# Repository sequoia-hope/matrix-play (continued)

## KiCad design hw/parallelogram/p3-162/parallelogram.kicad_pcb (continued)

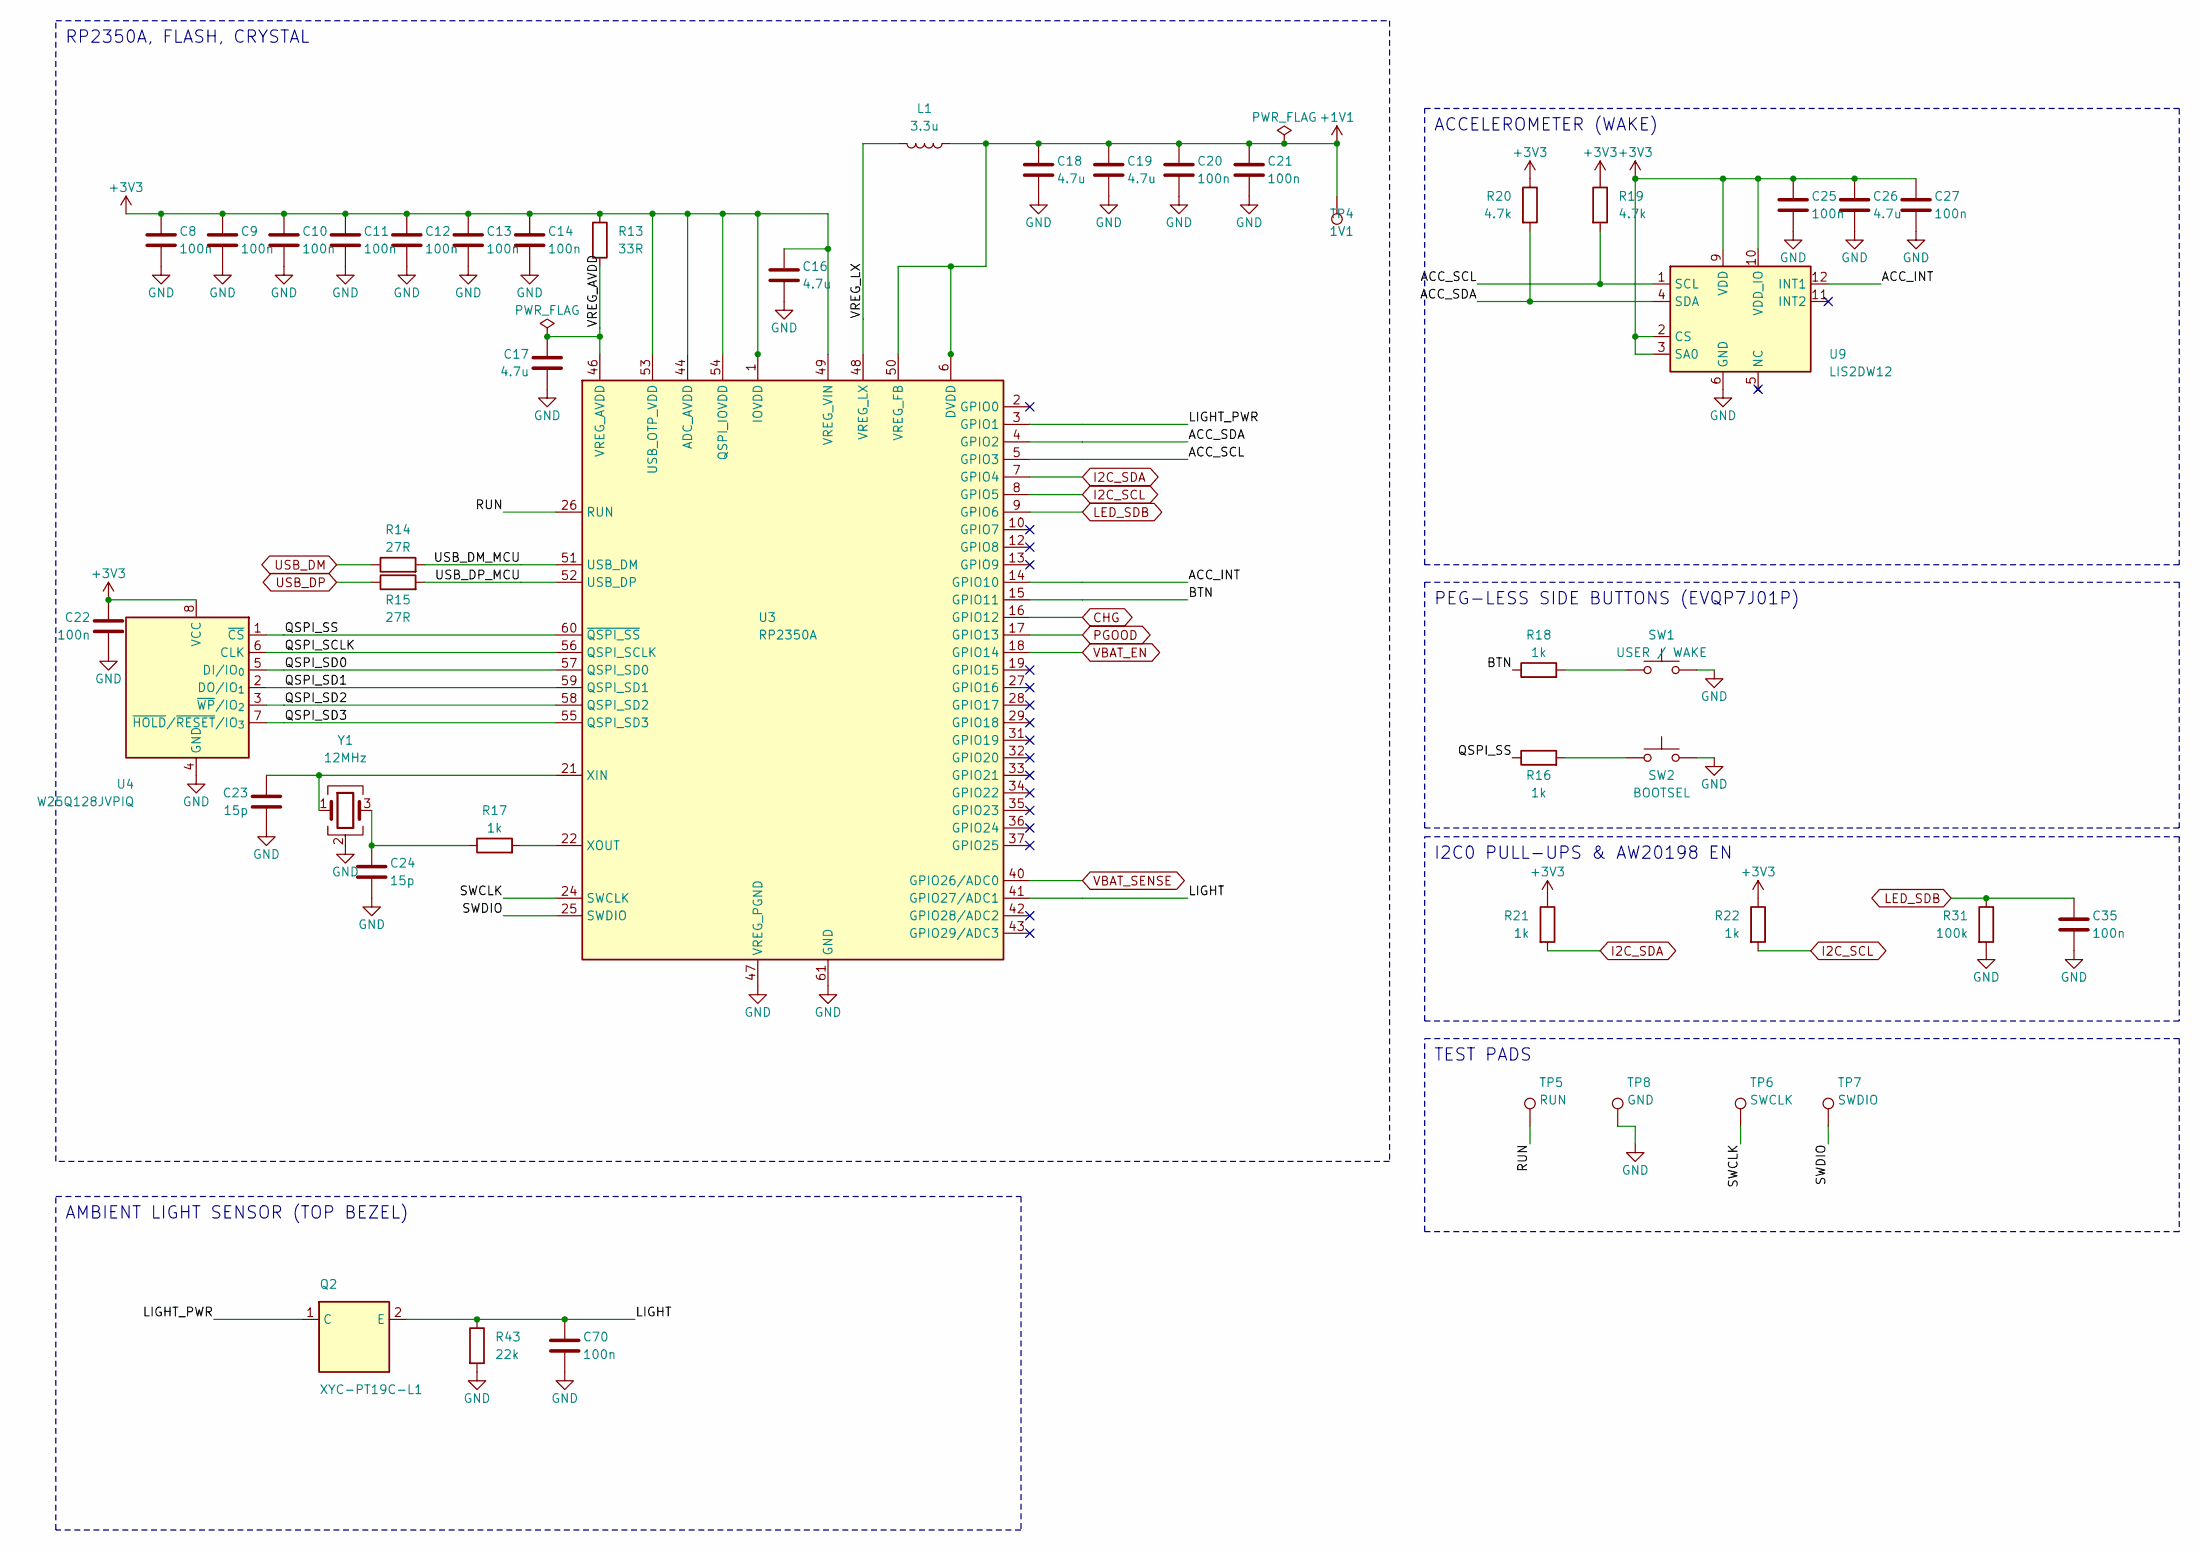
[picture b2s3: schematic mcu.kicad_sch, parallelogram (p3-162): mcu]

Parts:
C8, C9, C10, C11, C12, C13, C14, C20, C21, C22, C25, C27, C35, C70: 100n; C_0402_1005Metric; MPN CL05B104KO5NNNC; LCSC C1525
C16, C18: 4.7u; C_0402_1005Metric_small_pads; MPN CL05A475MP5NRNC; LCSC C23733
C17, C19, C26: 4.7u; C_0402_1005Metric; MPN CL05A475MP5NRNC; LCSC C23733
C23, C24: 15p; C_0402_1005Metric; MPN 0402CG150J500NT; LCSC C1548
L1: 3.3u; L_pol_2016; MPN AOTA-B201610S3R3-101-T; LCSC C42411119
Q2: XYC-PT19C-L1; SENSOR_ALS-PT19; MPN XYC-PT19C-L1; LCSC C2693594
R13: 33R; R_0402_1005Metric; MPN 0402WGF330JTCE; LCSC C25105
R14, R15: 27R; R_0402_1005Metric; MPN 0402WGF270JTCE; LCSC C25100
R16, R17, R18, R21, R22: 1k; R_0402_1005Metric; MPN 0402WGF1001TCE; LCSC C11702
R19, R20: 4.7k; R_0402_1005Metric; MPN 0402WGF4701TCE; LCSC C25900
R31: 100k; R_0402_1005Metric; MPN 0402WGF1003TCE; LCSC C25741
R43: 22k; R_0402_1005Metric; MPN 0402WGF2202TCE; LCSC C25768
SW1: USER / WAKE; SW_Panasonic_EVQP7J; MPN EVQP7J01P; LCSC C2828254
SW2: BOOTSEL; SW_Panasonic_EVQP7J; MPN EVQP7J01P; LCSC C2828254
TP4: 1V1; TestPoint_Pad_D1.0mm
TP5: RUN; TestPoint_Pad_D1.0mm
TP6: SWCLK; TestPoint_Pad_D1.0mm
TP7: SWDIO; TestPoint_Pad_D1.0mm
TP8: GND; TestPoint_Pad_D1.0mm
U3: RP2350A; RP2350-QFN-60-1EP_7x7_P0.4mm_EP3.4x3.4mm_ThermalVias; MPN RP2350A; LCSC C42411118
U4: W25Q128JVPIQ; WSON-8_6x5mm_P1.27mm_NoEPCopper; MPN W25Q128JVPIQ; LCSC C190862
U9: LIS2DW12; LGA-12_2x2mm_P0.5mm; MPN LIS2DW12TR; LCSC C189624
Y1: 12MHz; Crystal_SMD_3225-4Pin_3.2x2.5mm; MPN ABM8-272-T3; LCSC C20625731

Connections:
+3V3: C8.1, C9.1, C10.1, C11.1, C12.1, C13.1, C14.1, C16.1, C22.1, C25.1, C26.1, C27.1, R13.1, R19.1, R20.1, R21.1, R22.1, U3.1 (IOVDD), U3.11 (IOVDD), U3.20 (IOVDD), U3.30 (IOVDD), U3.38 (IOVDD), U3.44 (ADC_AVDD), U3.45 (IOVDD), U3.49 (VREG_VIN), U3.53 (USB_OTP_VDD), U3.54 (QSPI_IOVDD), U4.8 (VCC), U9.2 (CS), U9.3 (SA0), U9.9 (VDD), U9.10 (VDD_IO); also elsewhere on the board
/MCU/ACC_INT: U3.14 (GPIO10), U9.12 (INT1)
/MCU/ACC_SCL: R19.2, U3.5 (GPIO3), U9.1 (SCL)
/MCU/ACC_SDA: R20.2, U3.4 (GPIO2), U9.4 (SDA)
/MCU/BTN: R18.1, U3.15 (GPIO11)
/MCU/LIGHT: C70.1, Q2.2 (E), R43.1, U3.41 (GPIO27/ADC1)
/MCU/LIGHT_PWR: Q2.1 (C), U3.3 (GPIO1)
/MCU/QSPI_SCLK: U3.56 (QSPI_SCLK), U4.6 (CLK)
/MCU/QSPI_SD0: U3.57 (QSPI_SD0), U4.5 (DI/IO_{0})
/MCU/QSPI_SD1: U3.59 (QSPI_SD1), U4.2 (DO/IO_{1})
/MCU/QSPI_SD2: U3.58 (QSPI_SD2), U4.3 (~WP/IO_{2})
/MCU/QSPI_SD3: U3.55 (QSPI_SD3), U4.7 (~HOLD/~RESET/IO_{3})
/MCU/QSPI_SS: R16.1, U3.60 (~QSPI_SS), U4.1 (~CS)
/MCU/RUN: TP5.1, U3.26 (RUN)
/MCU/SWCLK: TP6.1, U3.24 (SWCLK)
/MCU/SWDIO: TP7.1, U3.25 (SWDIO)
/MCU/USB_DM_MCU: R14.2, U3.51 (USB_DM)
/MCU/USB_DP_MCU: R15.2, U3.52 (USB_DP)
/MCU/VREG_LX: L1.2, U3.48 (VREG_LX)
CHG: U3.16 (GPIO12); also elsewhere on the board
I2C_SCL: R22.2, U3.8 (GPIO5); also elsewhere on the board
I2C_SDA: R21.2, U3.7 (GPIO4); also elsewhere on the board
LED_SDB: C35.1, R31.1, U3.9 (GPIO6); also elsewhere on the board
unnamed: C24.1, R17.1, Y1.3
unnamed: R16.2, SW2.1
unnamed: R18.2, SW1.1
unnamed: C23.1, U3.21 (XIN), Y1.1
unnamed: R17.2, U3.22 (XOUT)
PGOOD: U3.17 (GPIO13); also elsewhere on the board
USB_DM: R14.1; also elsewhere on the board
USB_DP: R15.1; also elsewhere on the board
VBAT_EN: U3.18 (GPIO14); also elsewhere on the board
VBAT_SENSE: U3.40 (GPIO26/ADC0); also elsewhere on the board

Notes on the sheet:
RP2350A, FLASH, CRYSTAL
ACCELEROMETER (WAKE)
PEG-LESS SIDE BUTTONS (EVQP7J01P)
I2C0 PULL-UPS & AW20198 EN
TEST PADS
AMBIENT LIGHT SENSOR (TOP BEZEL)

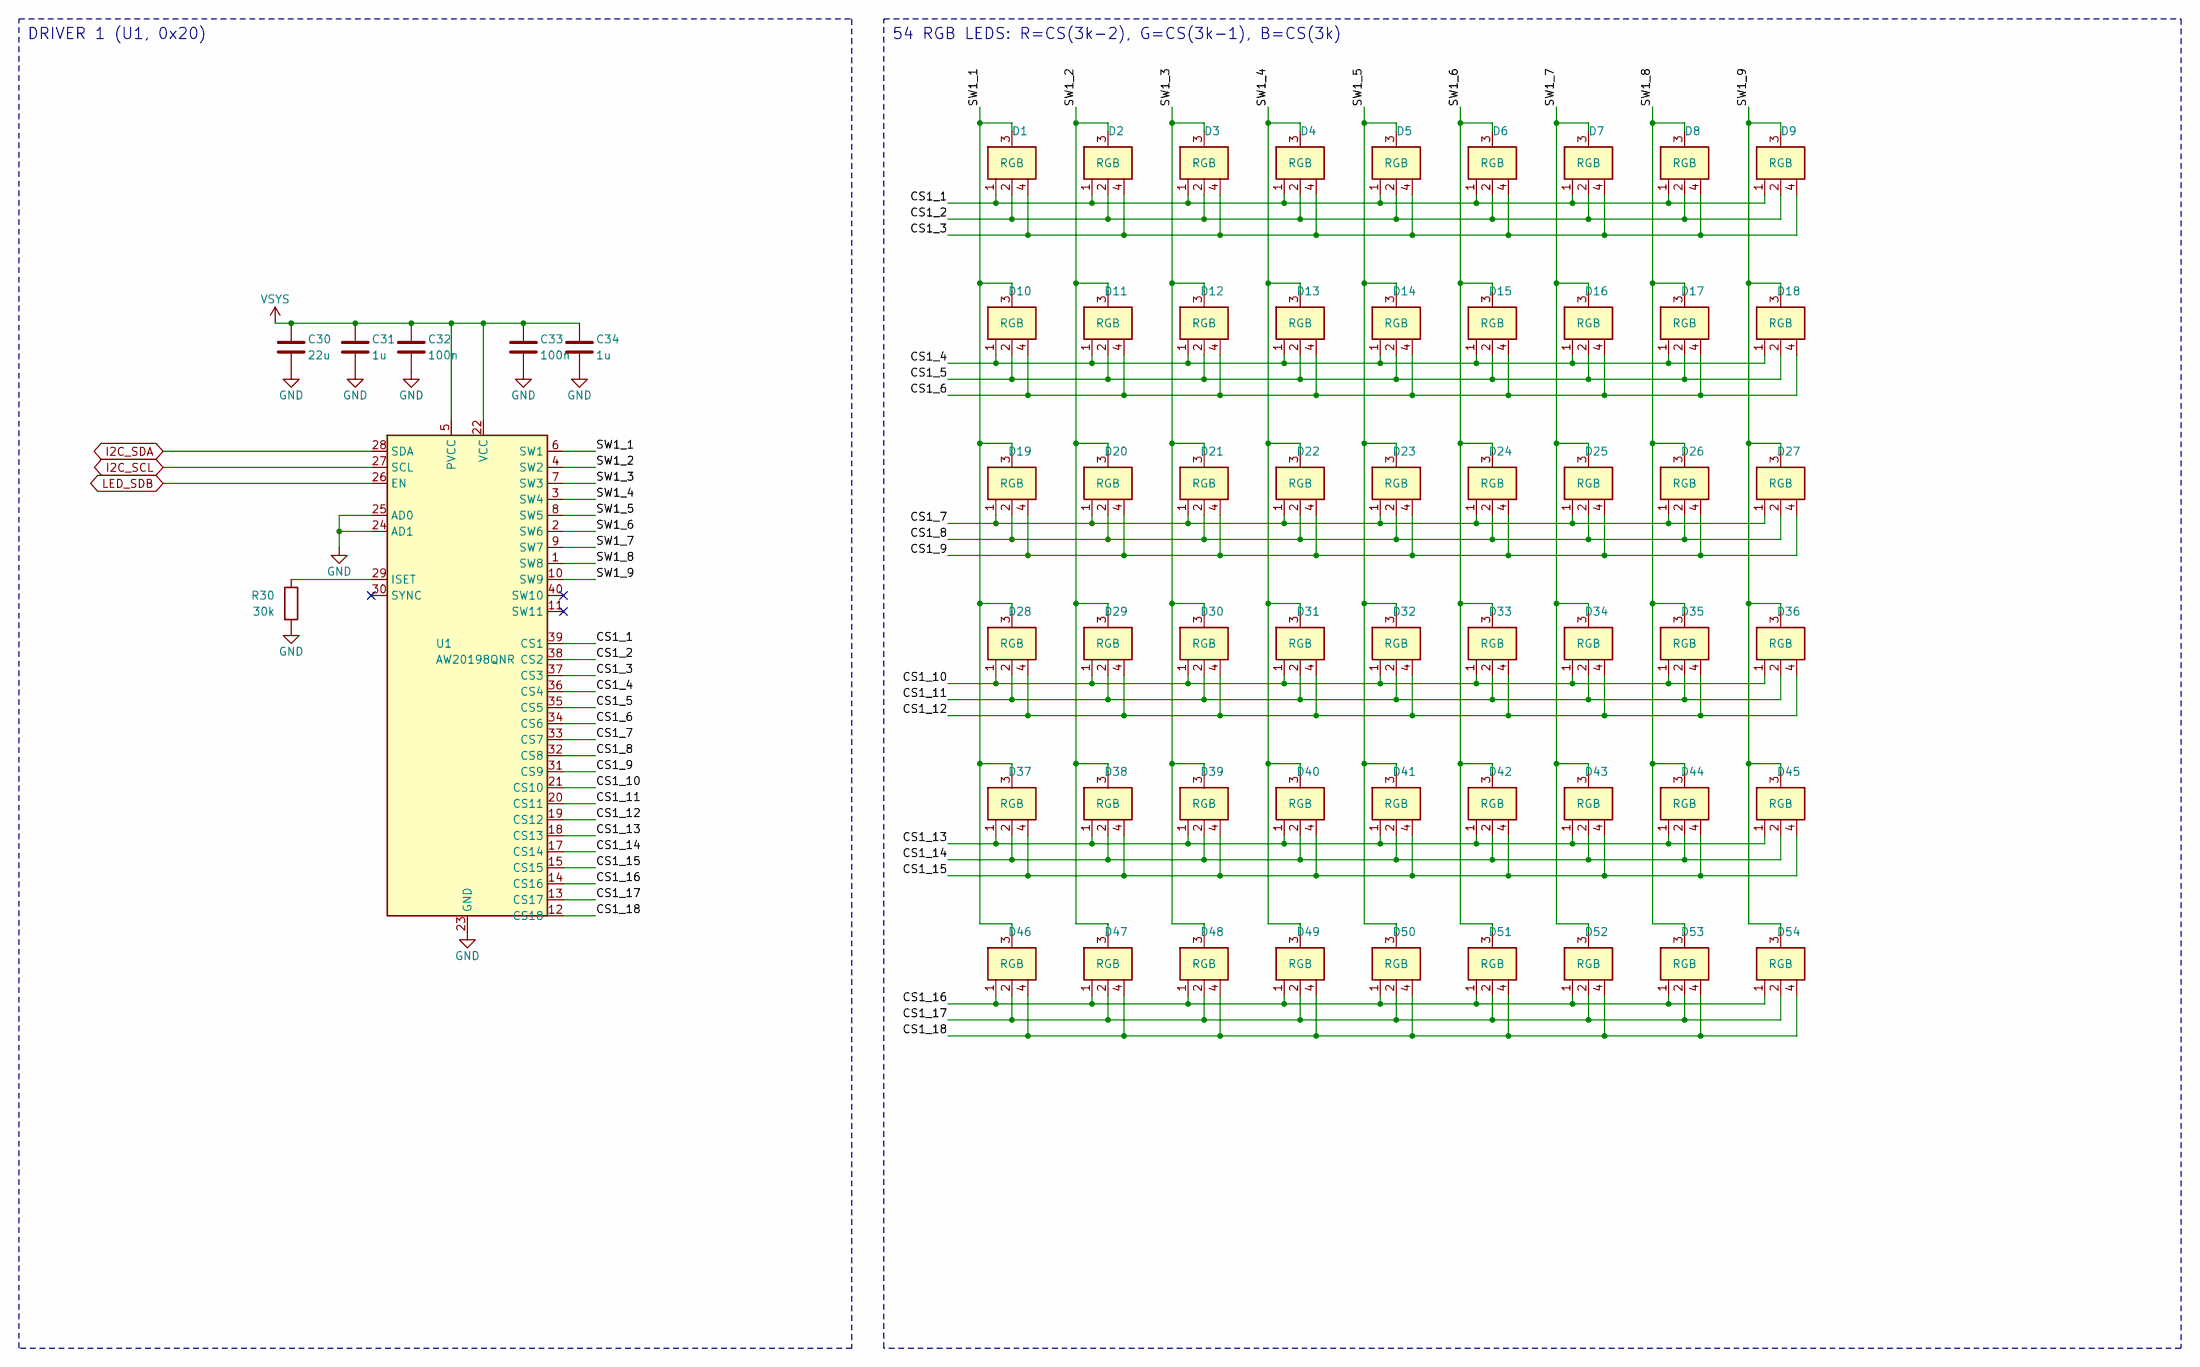
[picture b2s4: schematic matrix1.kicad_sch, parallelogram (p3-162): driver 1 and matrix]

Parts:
C30: 22u; C_0603_1608Metric; MPN CL10A226MP8NUNE; LCSC C86295
C31, C34: 1u; C_0402_1005Metric; MPN CL05A105KA5NQNC; LCSC C52923
C32, C33: 100n; C_0402_1005Metric; MPN CL05B104KO5NNNC; LCSC C1525
D1, D2, D3, D4, D5, D6, D7, D8, D9, D10, D11, D12, D13, D14, D15, D16, D17, D18, D19, D20, D21, D22, D23, D24, D25, D26, D27, D28, D29, D30, D31, D32, D33, D34, D35, D36, D37, D38, D39, D40, D41, D42, D43, D44, D45, D46, D47, D48, D49, D50, D51, D52, D53, D54: RGB; LED_XL-1010RGB; MPN XL-1010RGB-YG; LCSC C965834
R30: 30k; R_0402_1005Metric; MPN 0402WGF3002TCE; LCSC C25776
U1: AW20198QNR; AW20198_QFN-40-1EP_5x5mm_P0.4mm_EP3.4x3.4mm; MPN AW20198QNR; LCSC C5137654

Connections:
/Driver 1 and matrix/CS1_1: D1.1 (R), D2.1 (R), D3.1 (R), D4.1 (R), D5.1 (R), D6.1 (R), D7.1 (R), D8.1 (R), D9.1 (R), U1.39 (CS1)
/Driver 1 and matrix/CS1_2: D1.2 (G), D2.2 (G), D3.2 (G), D4.2 (G), D5.2 (G), D6.2 (G), D7.2 (G), D8.2 (G), D9.2 (G), U1.38 (CS2)
/Driver 1 and matrix/CS1_3: D1.4 (B), D2.4 (B), D3.4 (B), D4.4 (B), D5.4 (B), D6.4 (B), D7.4 (B), D8.4 (B), D9.4 (B), U1.37 (CS3)
/Driver 1 and matrix/CS1_4: D10.1 (R), D11.1 (R), D12.1 (R), D13.1 (R), D14.1 (R), D15.1 (R), D16.1 (R), D17.1 (R), D18.1 (R), U1.36 (CS4)
/Driver 1 and matrix/CS1_5: D10.2 (G), D11.2 (G), D12.2 (G), D13.2 (G), D14.2 (G), D15.2 (G), D16.2 (G), D17.2 (G), D18.2 (G), U1.35 (CS5)
/Driver 1 and matrix/CS1_6: D10.4 (B), D11.4 (B), D12.4 (B), D13.4 (B), D14.4 (B), D15.4 (B), D16.4 (B), D17.4 (B), D18.4 (B), U1.34 (CS6)
/Driver 1 and matrix/CS1_7: D19.1 (R), D20.1 (R), D21.1 (R), D22.1 (R), D23.1 (R), D24.1 (R), D25.1 (R), D26.1 (R), D27.1 (R), U1.33 (CS7)
/Driver 1 and matrix/CS1_8: D19.2 (G), D20.2 (G), D21.2 (G), D22.2 (G), D23.2 (G), D24.2 (G), D25.2 (G), D26.2 (G), D27.2 (G), U1.32 (CS8)
/Driver 1 and matrix/CS1_9: D19.4 (B), D20.4 (B), D21.4 (B), D22.4 (B), D23.4 (B), D24.4 (B), D25.4 (B), D26.4 (B), D27.4 (B), U1.31 (CS9)
/Driver 1 and matrix/CS1_10: D28.1 (R), D29.1 (R), D30.1 (R), D31.1 (R), D32.1 (R), D33.1 (R), D34.1 (R), D35.1 (R), D36.1 (R), U1.21 (CS10)
/Driver 1 and matrix/CS1_11: D28.2 (G), D29.2 (G), D30.2 (G), D31.2 (G), D32.2 (G), D33.2 (G), D34.2 (G), D35.2 (G), D36.2 (G), U1.20 (CS11)
/Driver 1 and matrix/CS1_12: D28.4 (B), D29.4 (B), D30.4 (B), D31.4 (B), D32.4 (B), D33.4 (B), D34.4 (B), D35.4 (B), D36.4 (B), U1.19 (CS12)
/Driver 1 and matrix/CS1_13: D37.1 (R), D38.1 (R), D39.1 (R), D40.1 (R), D41.1 (R), D42.1 (R), D43.1 (R), D44.1 (R), D45.1 (R), U1.18 (CS13)
/Driver 1 and matrix/CS1_14: D37.2 (G), D38.2 (G), D39.2 (G), D40.2 (G), D41.2 (G), D42.2 (G), D43.2 (G), D44.2 (G), D45.2 (G), U1.17 (CS14)
/Driver 1 and matrix/CS1_15: D37.4 (B), D38.4 (B), D39.4 (B), D40.4 (B), D41.4 (B), D42.4 (B), D43.4 (B), D44.4 (B), D45.4 (B), U1.15 (CS15)
/Driver 1 and matrix/CS1_16: D46.1 (R), D47.1 (R), D48.1 (R), D49.1 (R), D50.1 (R), D51.1 (R), D52.1 (R), D53.1 (R), D54.1 (R), U1.14 (CS16)
/Driver 1 and matrix/CS1_17: D46.2 (G), D47.2 (G), D48.2 (G), D49.2 (G), D50.2 (G), D51.2 (G), D52.2 (G), D53.2 (G), D54.2 (G), U1.13 (CS17)
/Driver 1 and matrix/CS1_18: D46.4 (B), D47.4 (B), D48.4 (B), D49.4 (B), D50.4 (B), D51.4 (B), D52.4 (B), D53.4 (B), D54.4 (B), U1.12 (CS18)
/Driver 1 and matrix/SW1_1: D1.3 (A), D10.3 (A), D19.3 (A), D28.3 (A), D37.3 (A), D46.3 (A), U1.6 (SW1)
/Driver 1 and matrix/SW1_2: D2.3 (A), D11.3 (A), D20.3 (A), D29.3 (A), D38.3 (A), D47.3 (A), U1.4 (SW2)
/Driver 1 and matrix/SW1_3: D3.3 (A), D12.3 (A), D21.3 (A), D30.3 (A), D39.3 (A), D48.3 (A), U1.7 (SW3)
/Driver 1 and matrix/SW1_4: D4.3 (A), D13.3 (A), D22.3 (A), D31.3 (A), D40.3 (A), D49.3 (A), U1.3 (SW4)
/Driver 1 and matrix/SW1_5: D5.3 (A), D14.3 (A), D23.3 (A), D32.3 (A), D41.3 (A), D50.3 (A), U1.8 (SW5)
/Driver 1 and matrix/SW1_6: D6.3 (A), D15.3 (A), D24.3 (A), D33.3 (A), D42.3 (A), D51.3 (A), U1.2 (SW6)
/Driver 1 and matrix/SW1_7: D7.3 (A), D16.3 (A), D25.3 (A), D34.3 (A), D43.3 (A), D52.3 (A), U1.9 (SW7)
/Driver 1 and matrix/SW1_8: D8.3 (A), D17.3 (A), D26.3 (A), D35.3 (A), D44.3 (A), D53.3 (A), U1.1 (SW8)
/Driver 1 and matrix/SW1_9: D9.3 (A), D18.3 (A), D27.3 (A), D36.3 (A), D45.3 (A), D54.3 (A), U1.10 (SW9)
I2C_SCL: U1.27 (SCL); also elsewhere on the board
I2C_SDA: U1.28 (SDA); also elsewhere on the board
LED_SDB: U1.26 (EN); also elsewhere on the board
unnamed: R30.1, U1.29 (ISET)
VSYS: C30.1, C31.1, C32.1, C33.1, C34.1, U1.5 (PVCC), U1.22 (VCC); also elsewhere on the board

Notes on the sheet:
DRIVER 1 (U1, 0x20)
54 RGB LEDS: R=CS(3k-2), G=CS(3k-1), B=CS(3k)

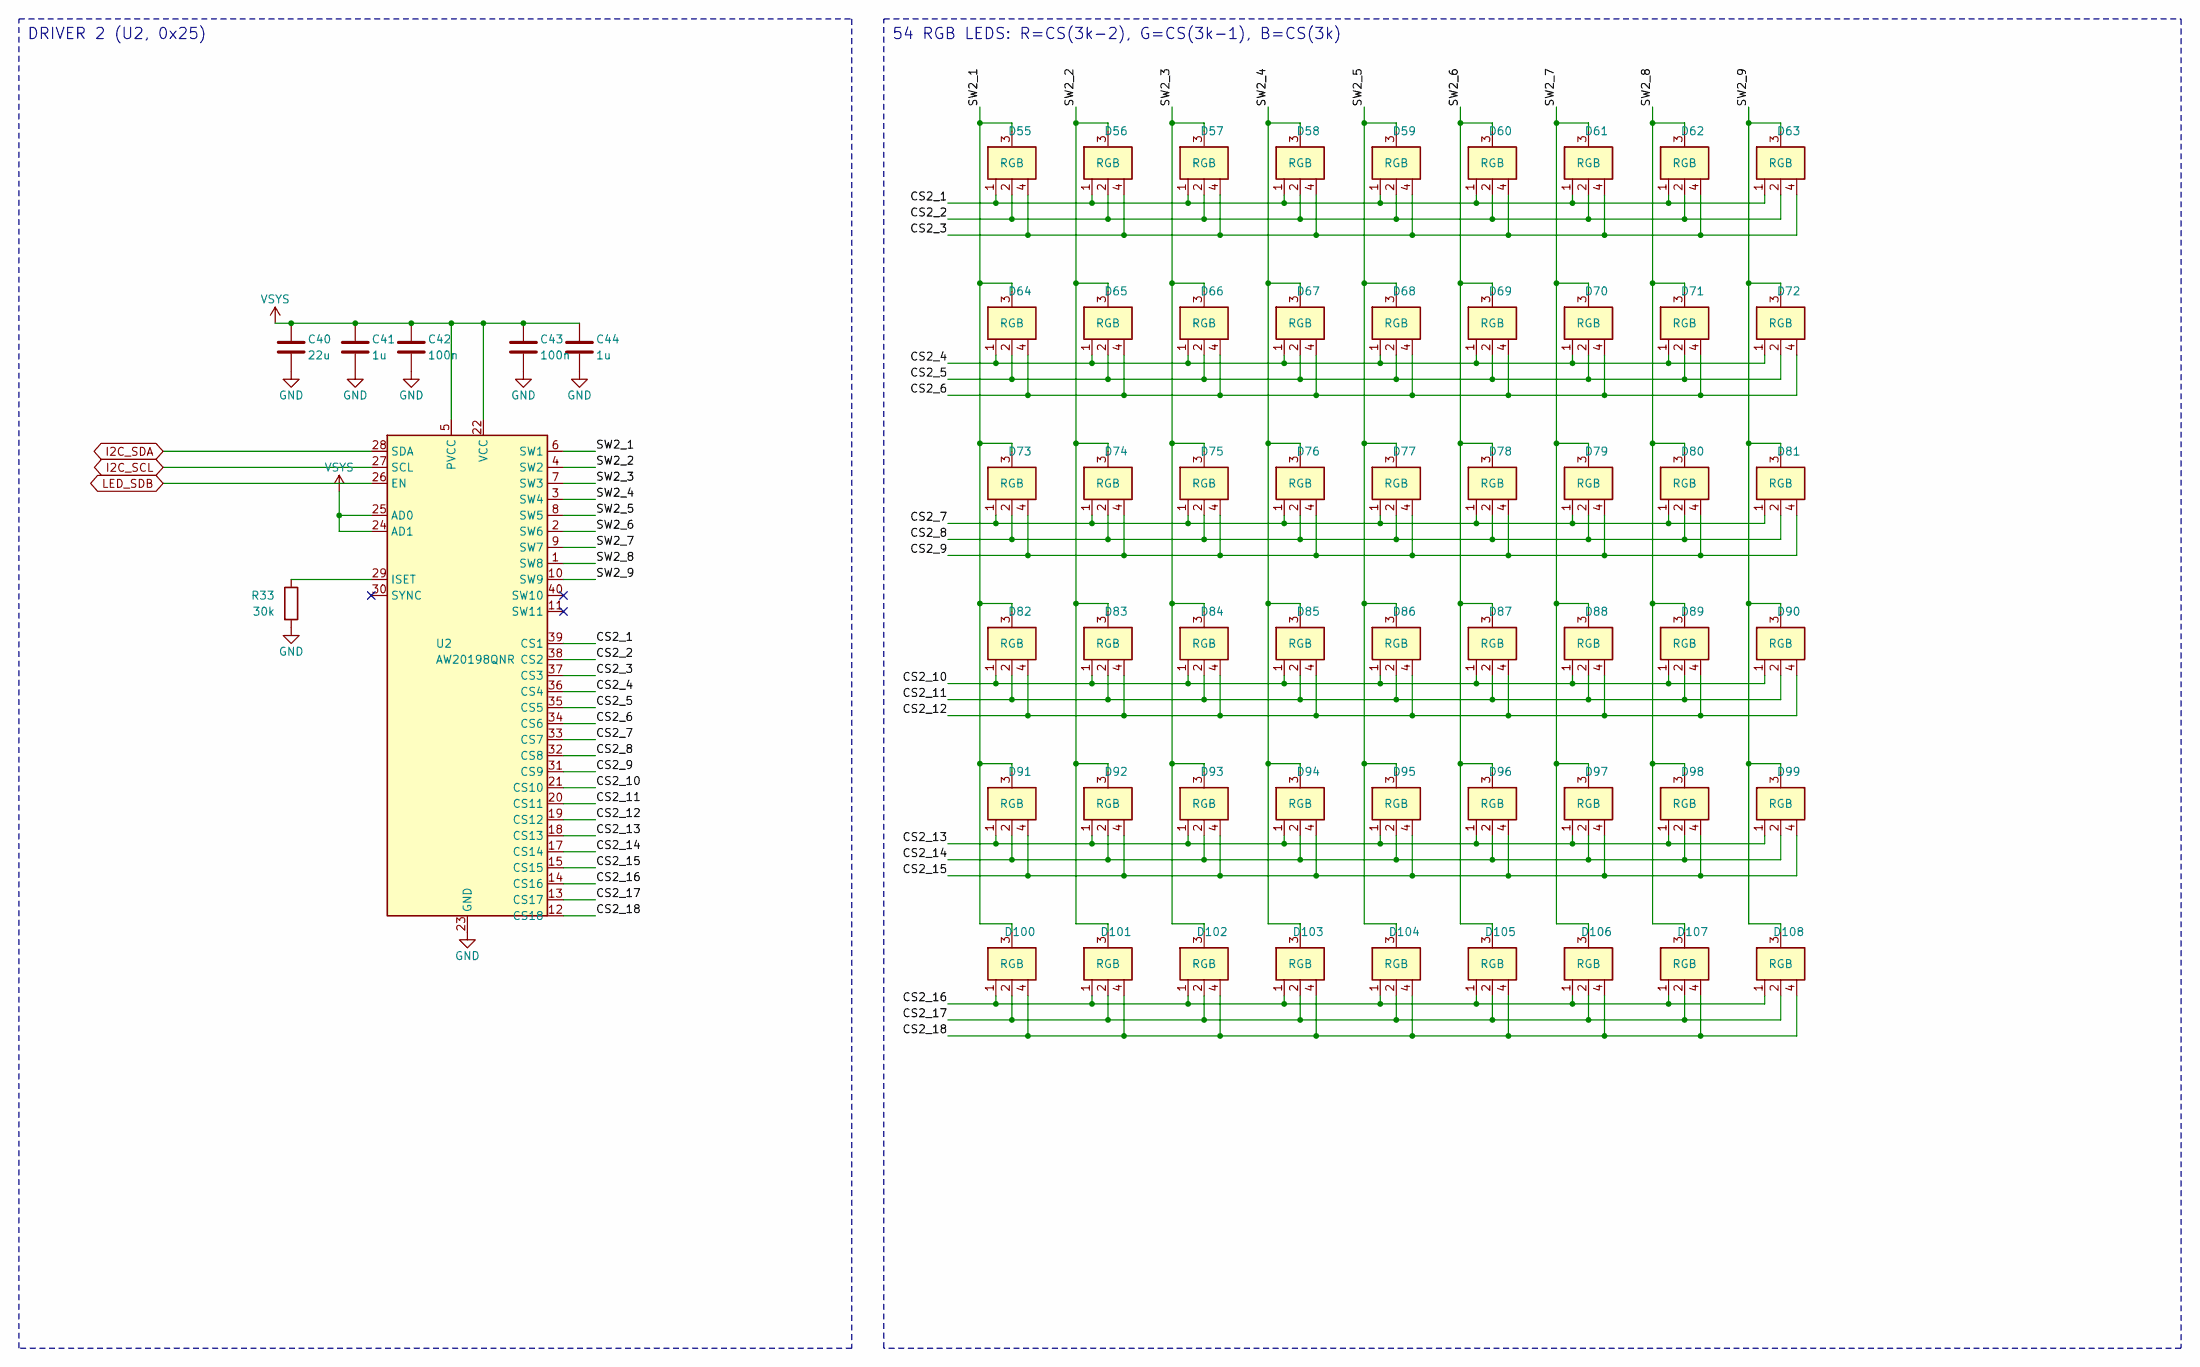
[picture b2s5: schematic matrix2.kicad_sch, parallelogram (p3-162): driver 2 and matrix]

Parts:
C40: 22u; C_0603_1608Metric; MPN CL10A226MP8NUNE; LCSC C86295
C41, C44: 1u; C_0402_1005Metric; MPN CL05A105KA5NQNC; LCSC C52923
C42, C43: 100n; C_0402_1005Metric; MPN CL05B104KO5NNNC; LCSC C1525
D55, D56, D57, D58, D59, D60, D61, D62, D63, D64, D65, D66, D67, D68, D69, D70, D71, D72, D73, D74, D75, D76, D77, D78, D79, D80, D81, D82, D83, D84, D85, D86, D87, D88, D89, D90, D91, D92, D93, D94, D95, D96, D97, D98, D99, D100, D101, D102, D103, D104, D105, D106, D107, D108: RGB; LED_XL-1010RGB; MPN XL-1010RGB-YG; LCSC C965834
R33: 30k; R_0402_1005Metric; MPN 0402WGF3002TCE; LCSC C25776
U2: AW20198QNR; AW20198_QFN-40-1EP_5x5mm_P0.4mm_EP3.4x3.4mm; MPN AW20198QNR; LCSC C5137654

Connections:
/Driver 2 and matrix/CS2_1: D55.1 (R), D56.1 (R), D57.1 (R), D58.1 (R), D59.1 (R), D60.1 (R), D61.1 (R), D62.1 (R), D63.1 (R), U2.39 (CS1)
/Driver 2 and matrix/CS2_2: D55.2 (G), D56.2 (G), D57.2 (G), D58.2 (G), D59.2 (G), D60.2 (G), D61.2 (G), D62.2 (G), D63.2 (G), U2.38 (CS2)
/Driver 2 and matrix/CS2_3: D55.4 (B), D56.4 (B), D57.4 (B), D58.4 (B), D59.4 (B), D60.4 (B), D61.4 (B), D62.4 (B), D63.4 (B), U2.37 (CS3)
/Driver 2 and matrix/CS2_4: D64.1 (R), D65.1 (R), D66.1 (R), D67.1 (R), D68.1 (R), D69.1 (R), D70.1 (R), D71.1 (R), D72.1 (R), U2.36 (CS4)
/Driver 2 and matrix/CS2_5: D64.2 (G), D65.2 (G), D66.2 (G), D67.2 (G), D68.2 (G), D69.2 (G), D70.2 (G), D71.2 (G), D72.2 (G), U2.35 (CS5)
/Driver 2 and matrix/CS2_6: D64.4 (B), D65.4 (B), D66.4 (B), D67.4 (B), D68.4 (B), D69.4 (B), D70.4 (B), D71.4 (B), D72.4 (B), U2.34 (CS6)
/Driver 2 and matrix/CS2_7: D73.1 (R), D74.1 (R), D75.1 (R), D76.1 (R), D77.1 (R), D78.1 (R), D79.1 (R), D80.1 (R), D81.1 (R), U2.33 (CS7)
/Driver 2 and matrix/CS2_8: D73.2 (G), D74.2 (G), D75.2 (G), D76.2 (G), D77.2 (G), D78.2 (G), D79.2 (G), D80.2 (G), D81.2 (G), U2.32 (CS8)
/Driver 2 and matrix/CS2_9: D73.4 (B), D74.4 (B), D75.4 (B), D76.4 (B), D77.4 (B), D78.4 (B), D79.4 (B), D80.4 (B), D81.4 (B), U2.31 (CS9)
/Driver 2 and matrix/CS2_10: D82.1 (R), D83.1 (R), D84.1 (R), D85.1 (R), D86.1 (R), D87.1 (R), D88.1 (R), D89.1 (R), D90.1 (R), U2.21 (CS10)
/Driver 2 and matrix/CS2_11: D82.2 (G), D83.2 (G), D84.2 (G), D85.2 (G), D86.2 (G), D87.2 (G), D88.2 (G), D89.2 (G), D90.2 (G), U2.20 (CS11)
/Driver 2 and matrix/CS2_12: D82.4 (B), D83.4 (B), D84.4 (B), D85.4 (B), D86.4 (B), D87.4 (B), D88.4 (B), D89.4 (B), D90.4 (B), U2.19 (CS12)
/Driver 2 and matrix/CS2_13: D91.1 (R), D92.1 (R), D93.1 (R), D94.1 (R), D95.1 (R), D96.1 (R), D97.1 (R), D98.1 (R), D99.1 (R), U2.18 (CS13)
/Driver 2 and matrix/CS2_14: D91.2 (G), D92.2 (G), D93.2 (G), D94.2 (G), D95.2 (G), D96.2 (G), D97.2 (G), D98.2 (G), D99.2 (G), U2.17 (CS14)
/Driver 2 and matrix/CS2_15: D91.4 (B), D92.4 (B), D93.4 (B), D94.4 (B), D95.4 (B), D96.4 (B), D97.4 (B), D98.4 (B), D99.4 (B), U2.15 (CS15)
/Driver 2 and matrix/CS2_16: D100.1 (R), D101.1 (R), D102.1 (R), D103.1 (R), D104.1 (R), D105.1 (R), D106.1 (R), D107.1 (R), D108.1 (R), U2.14 (CS16)
/Driver 2 and matrix/CS2_17: D100.2 (G), D101.2 (G), D102.2 (G), D103.2 (G), D104.2 (G), D105.2 (G), D106.2 (G), D107.2 (G), D108.2 (G), U2.13 (CS17)
/Driver 2 and matrix/CS2_18: D100.4 (B), D101.4 (B), D102.4 (B), D103.4 (B), D104.4 (B), D105.4 (B), D106.4 (B), D107.4 (B), D108.4 (B), U2.12 (CS18)
/Driver 2 and matrix/SW2_1: D55.3 (A), D64.3 (A), D73.3 (A), D82.3 (A), D91.3 (A), D100.3 (A), U2.6 (SW1)
/Driver 2 and matrix/SW2_2: D56.3 (A), D65.3 (A), D74.3 (A), D83.3 (A), D92.3 (A), D101.3 (A), U2.4 (SW2)
/Driver 2 and matrix/SW2_3: D57.3 (A), D66.3 (A), D75.3 (A), D84.3 (A), D93.3 (A), D102.3 (A), U2.7 (SW3)
/Driver 2 and matrix/SW2_4: D58.3 (A), D67.3 (A), D76.3 (A), D85.3 (A), D94.3 (A), D103.3 (A), U2.3 (SW4)
/Driver 2 and matrix/SW2_5: D59.3 (A), D68.3 (A), D77.3 (A), D86.3 (A), D95.3 (A), D104.3 (A), U2.8 (SW5)
/Driver 2 and matrix/SW2_6: D60.3 (A), D69.3 (A), D78.3 (A), D87.3 (A), D96.3 (A), D105.3 (A), U2.2 (SW6)
/Driver 2 and matrix/SW2_7: D61.3 (A), D70.3 (A), D79.3 (A), D88.3 (A), D97.3 (A), D106.3 (A), U2.9 (SW7)
/Driver 2 and matrix/SW2_8: D62.3 (A), D71.3 (A), D80.3 (A), D89.3 (A), D98.3 (A), D107.3 (A), U2.1 (SW8)
/Driver 2 and matrix/SW2_9: D63.3 (A), D72.3 (A), D81.3 (A), D90.3 (A), D99.3 (A), D108.3 (A), U2.10 (SW9)
I2C_SCL: U2.27 (SCL); also elsewhere on the board
I2C_SDA: U2.28 (SDA); also elsewhere on the board
LED_SDB: U2.26 (EN); also elsewhere on the board
unnamed: R33.1, U2.29 (ISET)
VSYS: C40.1, C41.1, C42.1, C43.1, C44.1, U2.5 (PVCC), U2.22 (VCC), U2.24 (AD1), U2.25 (AD0); also elsewhere on the board

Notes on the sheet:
DRIVER 2 (U2, 0x25)
54 RGB LEDS: R=CS(3k-2), G=CS(3k-1), B=CS(3k)

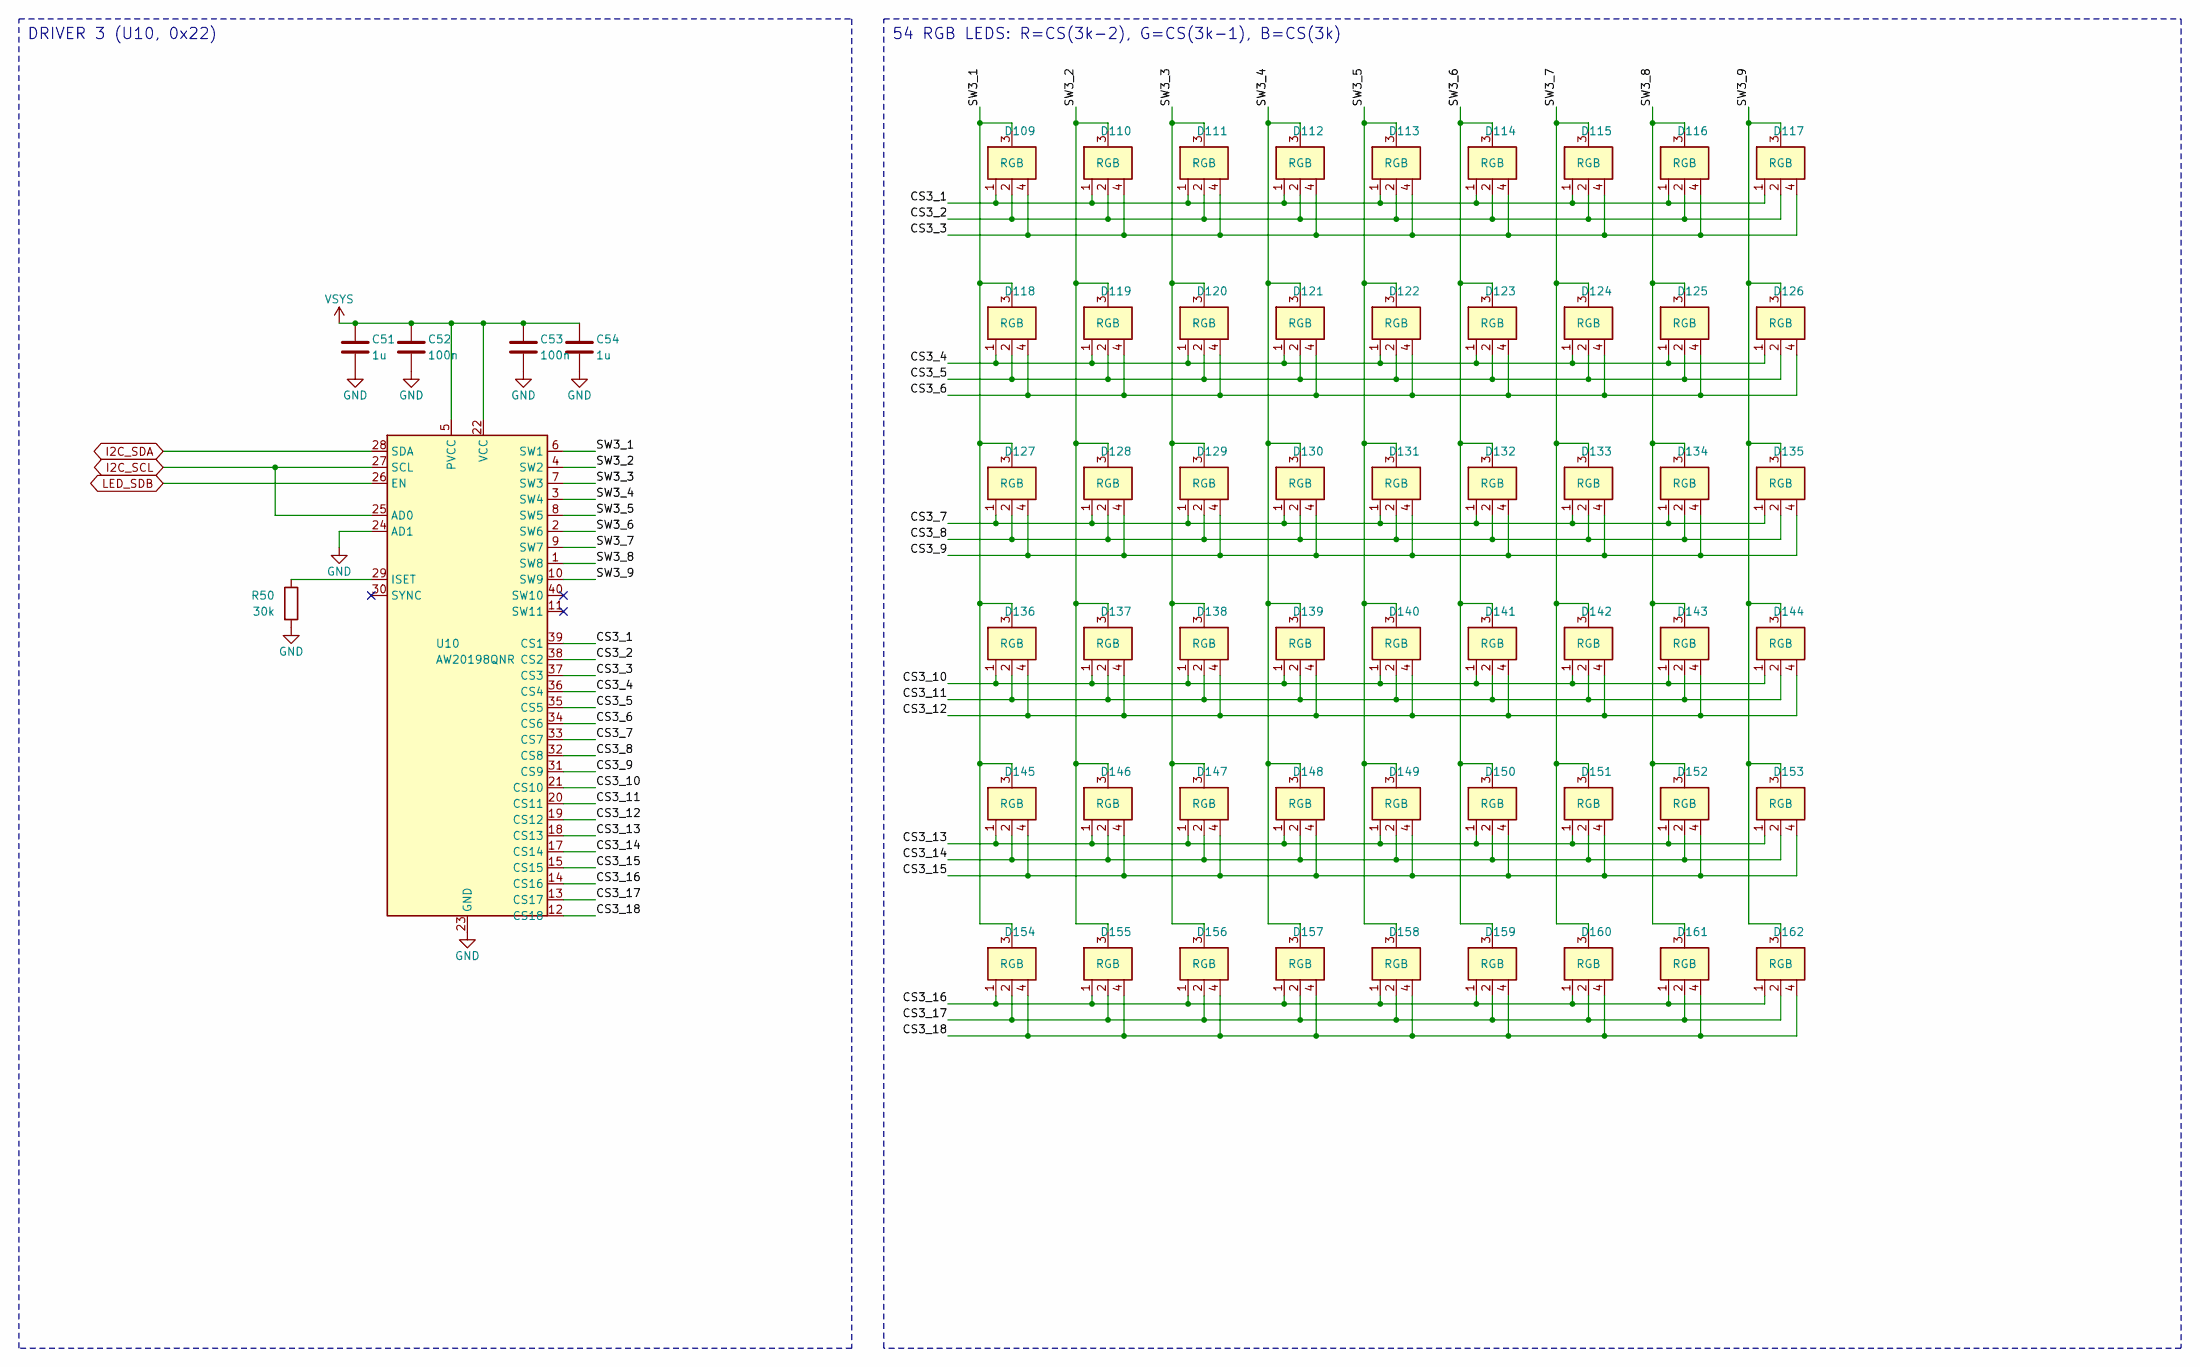
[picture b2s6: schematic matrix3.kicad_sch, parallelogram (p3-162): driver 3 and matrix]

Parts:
C51, C54: 1u; C_0402_1005Metric; MPN CL05A105KA5NQNC; LCSC C52923
C52, C53: 100n; C_0402_1005Metric; MPN CL05B104KO5NNNC; LCSC C1525
D109, D110, D111, D112, D113, D114, D115, D116, D117, D118, D119, D120, D121, D122, D123, D124, D125, D126, D127, D128, D129, D130, D131, D132, D133, D134, D135, D136, D137, D138, D139, D140, D141, D142, D143, D144, D145, D146, D147, D148, D149, D150, D151, D152, D153, D154, D155, D156, D157, D158, D159, D160, D161, D162: RGB; LED_XL-1010RGB; MPN XL-1010RGB-YG; LCSC C965834
R50: 30k; R_0402_1005Metric; MPN 0402WGF3002TCE; LCSC C25776
U10: AW20198QNR; AW20198_QFN-40-1EP_5x5mm_P0.4mm_EP3.4x3.4mm; MPN AW20198QNR; LCSC C5137654

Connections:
/Driver 3 and matrix/CS3_1: D109.1 (R), D110.1 (R), D111.1 (R), D112.1 (R), D113.1 (R), D114.1 (R), D115.1 (R), D116.1 (R), D117.1 (R), U10.39 (CS1)
/Driver 3 and matrix/CS3_2: D109.2 (G), D110.2 (G), D111.2 (G), D112.2 (G), D113.2 (G), D114.2 (G), D115.2 (G), D116.2 (G), D117.2 (G), U10.38 (CS2)
/Driver 3 and matrix/CS3_3: D109.4 (B), D110.4 (B), D111.4 (B), D112.4 (B), D113.4 (B), D114.4 (B), D115.4 (B), D116.4 (B), D117.4 (B), U10.37 (CS3)
/Driver 3 and matrix/CS3_4: D118.1 (R), D119.1 (R), D120.1 (R), D121.1 (R), D122.1 (R), D123.1 (R), D124.1 (R), D125.1 (R), D126.1 (R), U10.36 (CS4)
/Driver 3 and matrix/CS3_5: D118.2 (G), D119.2 (G), D120.2 (G), D121.2 (G), D122.2 (G), D123.2 (G), D124.2 (G), D125.2 (G), D126.2 (G), U10.35 (CS5)
/Driver 3 and matrix/CS3_6: D118.4 (B), D119.4 (B), D120.4 (B), D121.4 (B), D122.4 (B), D123.4 (B), D124.4 (B), D125.4 (B), D126.4 (B), U10.34 (CS6)
/Driver 3 and matrix/CS3_7: D127.1 (R), D128.1 (R), D129.1 (R), D130.1 (R), D131.1 (R), D132.1 (R), D133.1 (R), D134.1 (R), D135.1 (R), U10.33 (CS7)
/Driver 3 and matrix/CS3_8: D127.2 (G), D128.2 (G), D129.2 (G), D130.2 (G), D131.2 (G), D132.2 (G), D133.2 (G), D134.2 (G), D135.2 (G), U10.32 (CS8)
/Driver 3 and matrix/CS3_9: D127.4 (B), D128.4 (B), D129.4 (B), D130.4 (B), D131.4 (B), D132.4 (B), D133.4 (B), D134.4 (B), D135.4 (B), U10.31 (CS9)
/Driver 3 and matrix/CS3_10: D136.1 (R), D137.1 (R), D138.1 (R), D139.1 (R), D140.1 (R), D141.1 (R), D142.1 (R), D143.1 (R), D144.1 (R), U10.21 (CS10)
/Driver 3 and matrix/CS3_11: D136.2 (G), D137.2 (G), D138.2 (G), D139.2 (G), D140.2 (G), D141.2 (G), D142.2 (G), D143.2 (G), D144.2 (G), U10.20 (CS11)
/Driver 3 and matrix/CS3_12: D136.4 (B), D137.4 (B), D138.4 (B), D139.4 (B), D140.4 (B), D141.4 (B), D142.4 (B), D143.4 (B), D144.4 (B), U10.19 (CS12)
/Driver 3 and matrix/CS3_13: D145.1 (R), D146.1 (R), D147.1 (R), D148.1 (R), D149.1 (R), D150.1 (R), D151.1 (R), D152.1 (R), D153.1 (R), U10.18 (CS13)
/Driver 3 and matrix/CS3_14: D145.2 (G), D146.2 (G), D147.2 (G), D148.2 (G), D149.2 (G), D150.2 (G), D151.2 (G), D152.2 (G), D153.2 (G), U10.17 (CS14)
/Driver 3 and matrix/CS3_15: D145.4 (B), D146.4 (B), D147.4 (B), D148.4 (B), D149.4 (B), D150.4 (B), D151.4 (B), D152.4 (B), D153.4 (B), U10.15 (CS15)
/Driver 3 and matrix/CS3_16: D154.1 (R), D155.1 (R), D156.1 (R), D157.1 (R), D158.1 (R), D159.1 (R), D160.1 (R), D161.1 (R), D162.1 (R), U10.14 (CS16)
/Driver 3 and matrix/CS3_17: D154.2 (G), D155.2 (G), D156.2 (G), D157.2 (G), D158.2 (G), D159.2 (G), D160.2 (G), D161.2 (G), D162.2 (G), U10.13 (CS17)
/Driver 3 and matrix/CS3_18: D154.4 (B), D155.4 (B), D156.4 (B), D157.4 (B), D158.4 (B), D159.4 (B), D160.4 (B), D161.4 (B), D162.4 (B), U10.12 (CS18)
/Driver 3 and matrix/SW3_1: D109.3 (A), D118.3 (A), D127.3 (A), D136.3 (A), D145.3 (A), D154.3 (A), U10.6 (SW1)
/Driver 3 and matrix/SW3_2: D110.3 (A), D119.3 (A), D128.3 (A), D137.3 (A), D146.3 (A), D155.3 (A), U10.4 (SW2)
/Driver 3 and matrix/SW3_3: D111.3 (A), D120.3 (A), D129.3 (A), D138.3 (A), D147.3 (A), D156.3 (A), U10.7 (SW3)
/Driver 3 and matrix/SW3_4: D112.3 (A), D121.3 (A), D130.3 (A), D139.3 (A), D148.3 (A), D157.3 (A), U10.3 (SW4)
/Driver 3 and matrix/SW3_5: D113.3 (A), D122.3 (A), D131.3 (A), D140.3 (A), D149.3 (A), D158.3 (A), U10.8 (SW5)
/Driver 3 and matrix/SW3_6: D114.3 (A), D123.3 (A), D132.3 (A), D141.3 (A), D150.3 (A), D159.3 (A), U10.2 (SW6)
/Driver 3 and matrix/SW3_7: D115.3 (A), D124.3 (A), D133.3 (A), D142.3 (A), D151.3 (A), D160.3 (A), U10.9 (SW7)
/Driver 3 and matrix/SW3_8: D116.3 (A), D125.3 (A), D134.3 (A), D143.3 (A), D152.3 (A), D161.3 (A), U10.1 (SW8)
/Driver 3 and matrix/SW3_9: D117.3 (A), D126.3 (A), D135.3 (A), D144.3 (A), D153.3 (A), D162.3 (A), U10.10 (SW9)
I2C_SCL: U10.25 (AD0), U10.27 (SCL); also elsewhere on the board
I2C_SDA: U10.28 (SDA); also elsewhere on the board
LED_SDB: U10.26 (EN); also elsewhere on the board
unnamed: R50.1, U10.29 (ISET)
VSYS: C51.1, C52.1, C53.1, C54.1, U10.5 (PVCC), U10.22 (VCC); also elsewhere on the board

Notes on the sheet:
DRIVER 3 (U10, 0x22)
54 RGB LEDS: R=CS(3k-2), G=CS(3k-1), B=CS(3k)

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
